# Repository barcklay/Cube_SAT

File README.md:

# HAB-1 — a homemade flight computer for a stratospheric balloon

HAB-1 is an experimental payload for a high-altitude weather balloon. It will climb to
about **30 km**, record what happens on the way up, fall back under a parachute, and then
has to be found on the ground. First flight planned in **Thailand, February–March 2027**.

**Interactive 3D model:** https://claude.ai/artifact/VP8YPhxGNXckYP5Keu93rK
— scrub through the flight, open the box and look at the board inside.
**Code and design files:** https://github.com/barcklay/Cube_SAT (this repository)

<!-- PHOTOS: add docs/photos/bench_top.jpg, docs/photos/modules.jpg, docs/photos/telemetry.jpg
     and a short video link here (Linear HW-157). -->

## About me

I'm Ilzira Badretdinova. I have lived in Bangkok for four years. I design HAB-1 on my own —
the electronics, the firmware, the circuit board and the enclosure — and I would like to
fly it for the first time **together with an experienced team**.

## What already works

Everything below runs today on the bench (NUCLEO-G474RE development board + breadboard
with the real sensor modules) and has been tested:

| Part | What it does | Status |
|---|---|---|
| **STM32G474** firmware | reads all sensors 5 times a second, one telemetry frame every 200 ms | ✅ tested |
| **Barometer** BMP390 | pressure, temperature, altitude (layered standard atmosphere, 0–47 km) | ✅ tested |
| **IMU** ICM-42688 | acceleration and rotation: swing, burst, parachute opening | ✅ tested |
| **GPS** u-blox MAX-M10S | position and altitude; set to *Airborne <4g* so it keeps working above 12 km | ✅ tested on the ground |
| **Outside temperature** DS18B20 | air temperature through the box wall | ✅ tested |
| **Black box** 16 MB SPI flash | every frame logged with a CRC; survives power cuts and resets | ✅ tested |
| **Watchdog + sensor recovery** | a hung program restarts in 2 s; a lost sensor is marked and retried every 5 s | ✅ tested by pulling wires live |
| **Flight state machine** | PRELAUNCH → ASCENT → FLOAT → BURST → DESCENT → LANDED; continues after a reset in flight | ✅ tested in simulation, on the laptop and in a lift |

## Still in development / not tested yet

| Part | Status |
|---|---|
| **LoRa radio** E22-400M22S (433 MHz) and the ground station | ⏳ parts on the way, not brought up yet |
| **Flight PCB** — 4-layer CubeSat 1U board, modules on sockets | designed and routed (ERC/DRC clean), ⏳ independent review, then manufacture |
| **Enclosure** — foam box with a 3D-printed sled | concept ready, not built |
| **Cold test** (dry ice, −60 °C), drop test, tethered flight | ⏳ planned |
| **Backup tracker, recovery buzzer, parachute** | ⏳ to buy / to build |

## Main parameters (preliminary)

| | |
|---|---|
| Payload mass | **≈ 400–600 g** (estimate: ~400 g without a camera, ~600 g with one); weighed after assembly |
| Payload size | **≈ 250 × 175 × 140 mm**, orange foam box (XPS, 30 mm walls) |
| Flight board | 95.9 × 90.2 mm (CubeSat 1U), STM32G474RET6 |
| Power | 4 × Energizer L91 lithium AA (work down to −40 °C), 3.3 V regulator |
| Radio | LoRa 433 MHz (E22-400M22S); output power to be set within Thai (NBTC) limits |
| Tracking and recovery | GPS position over LoRa during the flight; separate backup GPS/SIM tracker with its own battery; buzzer after landing; contact label on the box |
| Balloon / parachute | latex balloon, burst at ~30 km expected; parachute for ~5 m/s at the ground (not chosen yet) |
| Expected flight | ~1 h 40 min up, ~45 min down, landing 30–80 km from the launch point (depends on winds) |

## What the flight should prove

1. The flight computer works end to end in real conditions: cold, low pressure,
   vibration at burst — and recognises every phase of the flight on its own.
2. The black box records the whole flight without gaps.
3. Radio telemetry reaches the ground station, and the payload can be tracked and found.
4. A measured temperature and pressure profile of the tropical atmosphere up to ~30 km
   (the tropopause over Thailand is colder than −75 °C).
5. Photos of the horizon from the stratosphere (if a camera flies).

## What I'm looking for

- **A joint launch**, or a place for HAB-1 in an existing balloon mission.
- **A technical review** of the payload by people who have flown before.
- **Help with permissions**: CAAT (unmanned free balloon), NOTAM, and the radio.
  **I do not have a flight permission yet.**

## Things I found and fixed along the way

- The usual barometric formula is only valid below 11 km: at 30 km it reads **~4.7 km too
  low**. The firmware now uses the layered standard atmosphere.
- A pulled DS18B20 wire read as a perfectly valid **0.0 °C** (all-zero data passes the CRC).
  The firmware now checks bits the sensor always sets.
- The IMU breakout corrupted the flash on a shared SPI bus, so each has its own bus.
- Two of five sensor modules had a different pin order than expected; every socket on the
  PCB was checked against the real module before routing.

## Repository

| Folder | What is inside |
|---|---|
| `hab_bringup/` | STM32 firmware (STM32CubeMX + CMake). Flight logic in `Core/Inc/flight_sm.h` |
| `tools/` | live telemetry viewer, ground station, log download, flashing, the lift test, the state machine test |
| `hardware/flight_pcb/` | flight board: spec, schematic and PCB **generated by Python scripts**, auto-routing with Freerouting, checks |
| `mission/launch_site/` | how the launch site was chosen: airports, military areas, borders, terrain, predicted landing points |
| `portfolio/lab/` | the interactive 3D page |
| `bmp390_altitude/`, `flash_boot_counter/`, `FlashCard/` | first bring-up experiments |

## How it is checked

- **Firmware:** `tools/test_flight_sm.c` flies 10 synthetic balloons through the state
  machine (normal flight, noisy sensor, slow leak, 3 h float, reset in flight,
  stop-and-go ascent…); an accelerated fake flight runs on the real board (`S` command).
- **Board:** KiCad ERC and DRC, a netlist check against the generator's tables, and
  schematic-to-PCB parity — all clean before a change is committed.

```sh
python3 tools/telemetry.py          # live view of the board over USB
python3 tools/logdump.py            # download the black box as CSV
python3 tools/ground_station.py --demo   # ground station on a made-up flight: map, altitude, signal
python3 tools/test_ground_station.py     # packet decoding checked against the firmware's own C code
cc -O2 -o /tmp/t tools/test_flight_sm.c -lm && /tmp/t   # state machine tests
cc -O2 -o /tmp/a tools/test_altitude.c -lm && /tmp/a    # barometer + GPS altitude: flights to 33 km, GPS gaps
cc -O2 -o /tmp/o tools/test_oled.c -lm && /tmp/o        # bench OLED: screens and the piecewise update
```

## Contact

Ilzira Badretdinova, Bangkok · **ilzira.reads@gmail.com** · or open an issue in this repository.

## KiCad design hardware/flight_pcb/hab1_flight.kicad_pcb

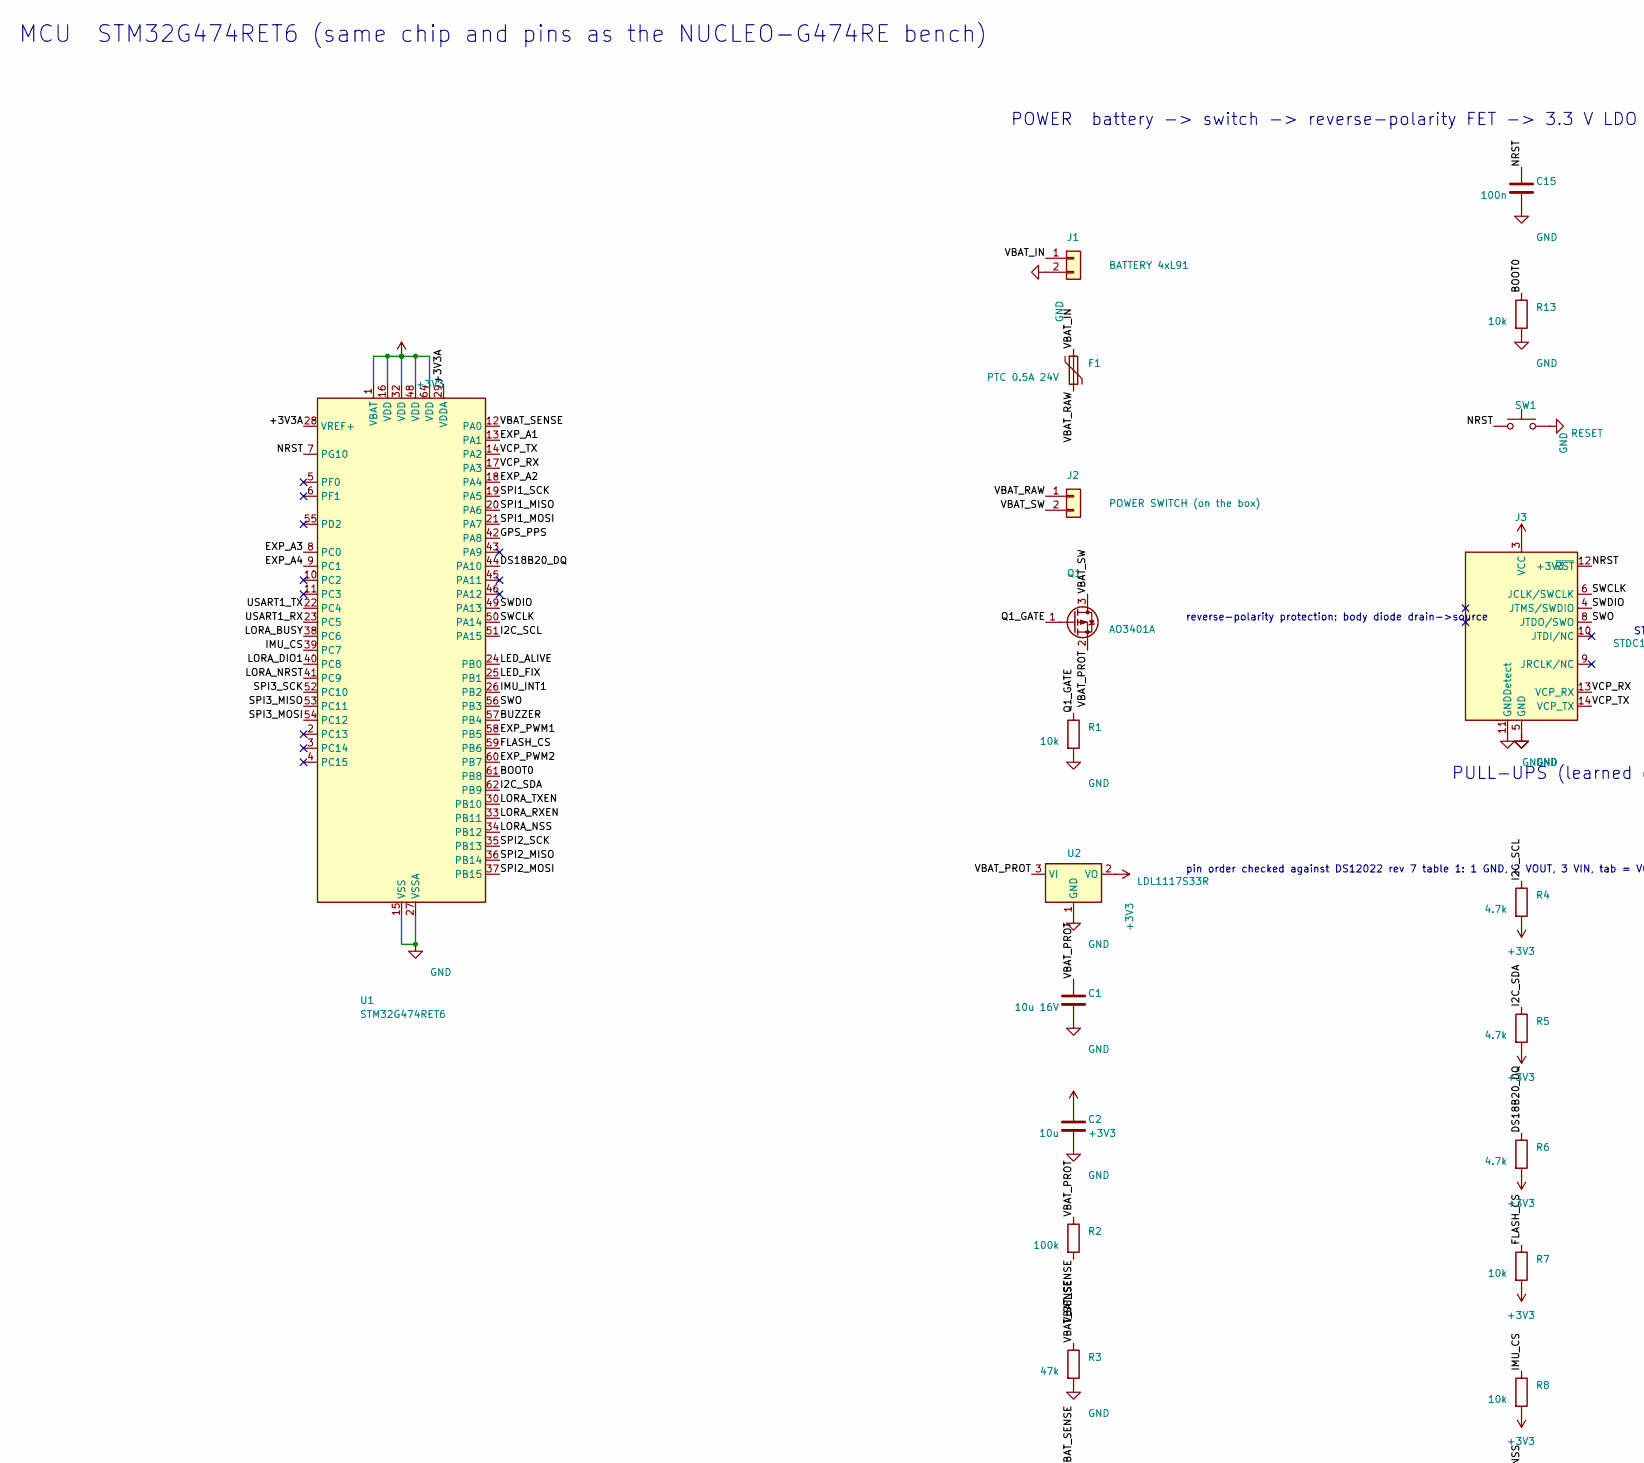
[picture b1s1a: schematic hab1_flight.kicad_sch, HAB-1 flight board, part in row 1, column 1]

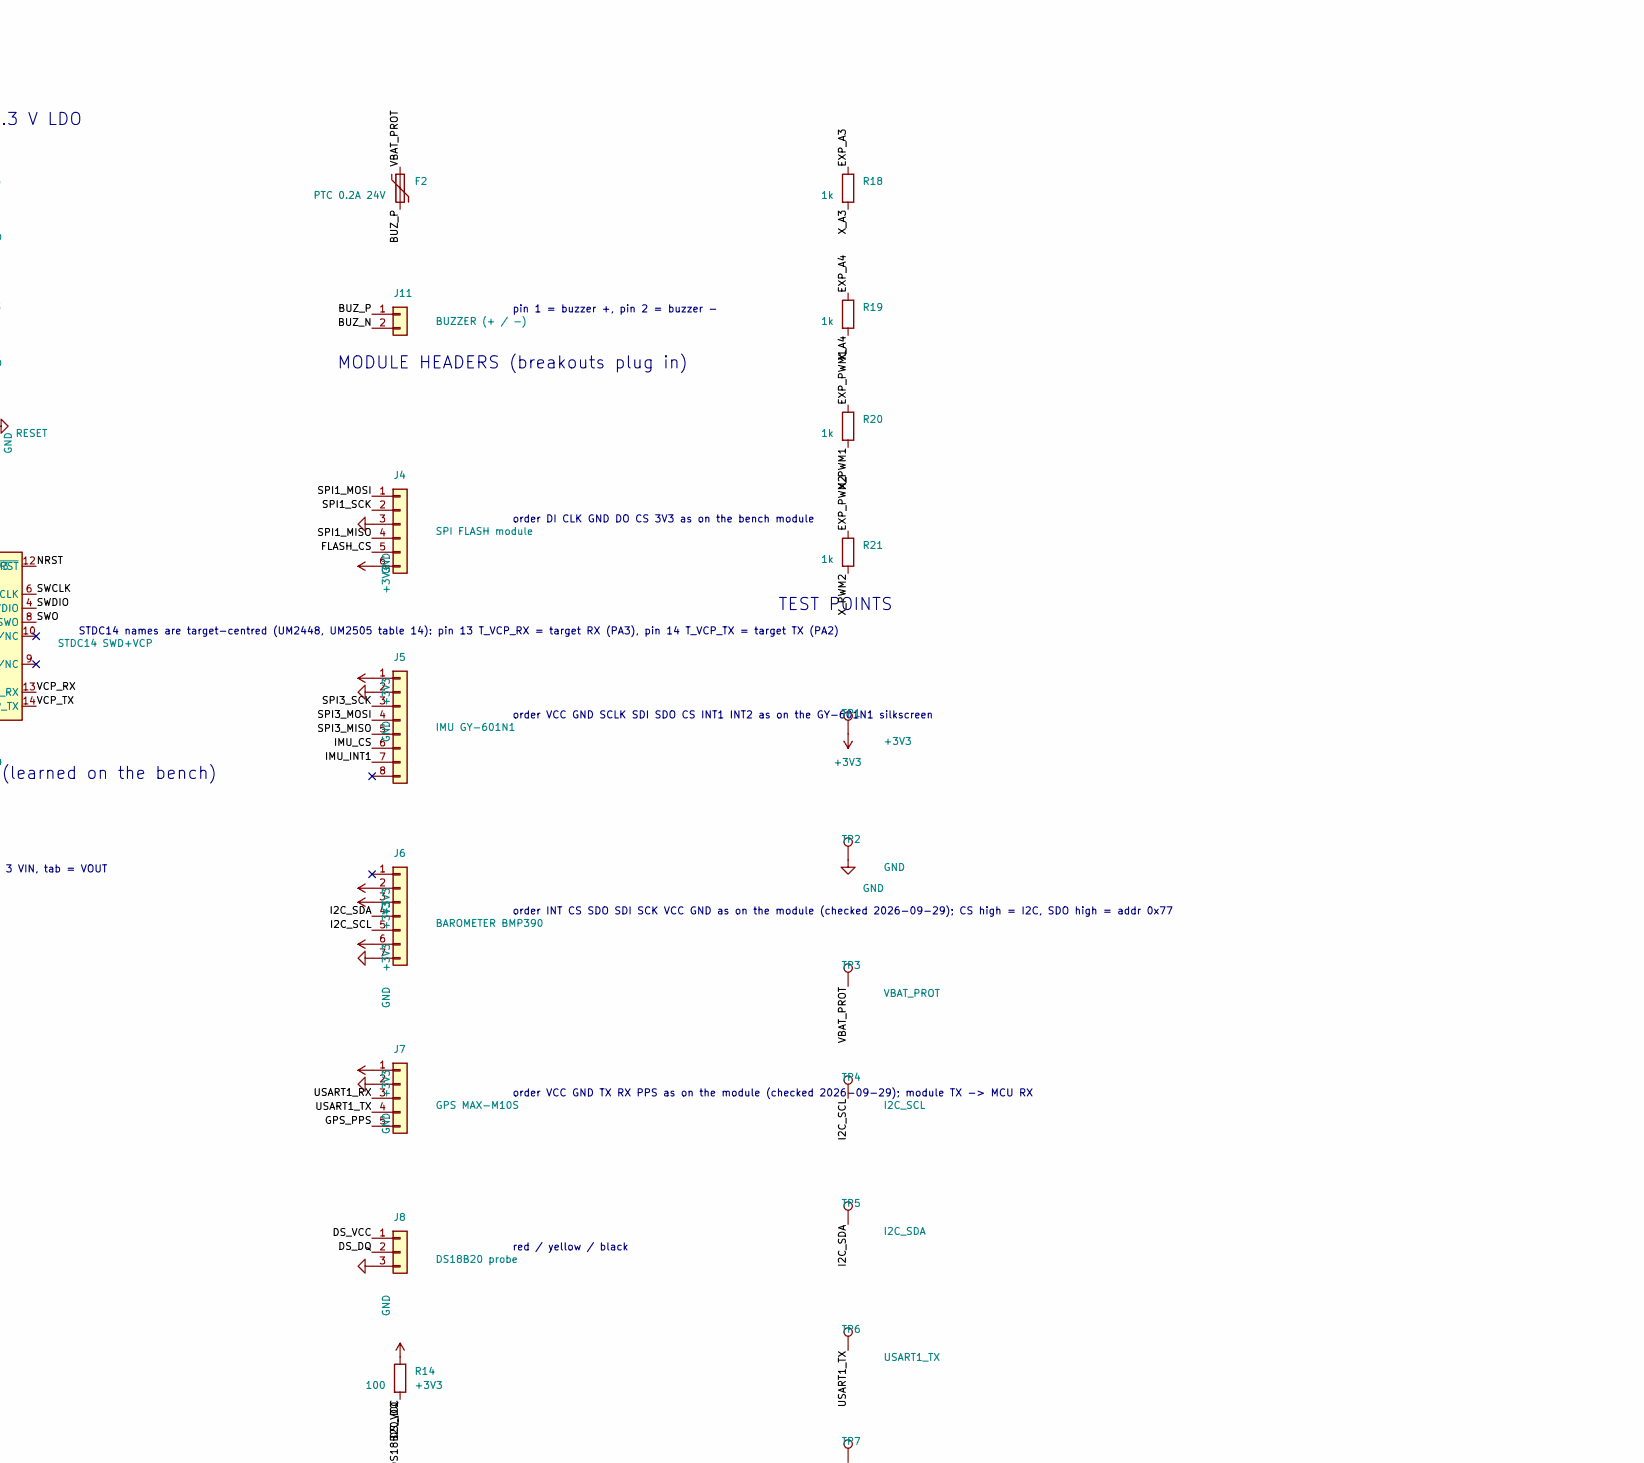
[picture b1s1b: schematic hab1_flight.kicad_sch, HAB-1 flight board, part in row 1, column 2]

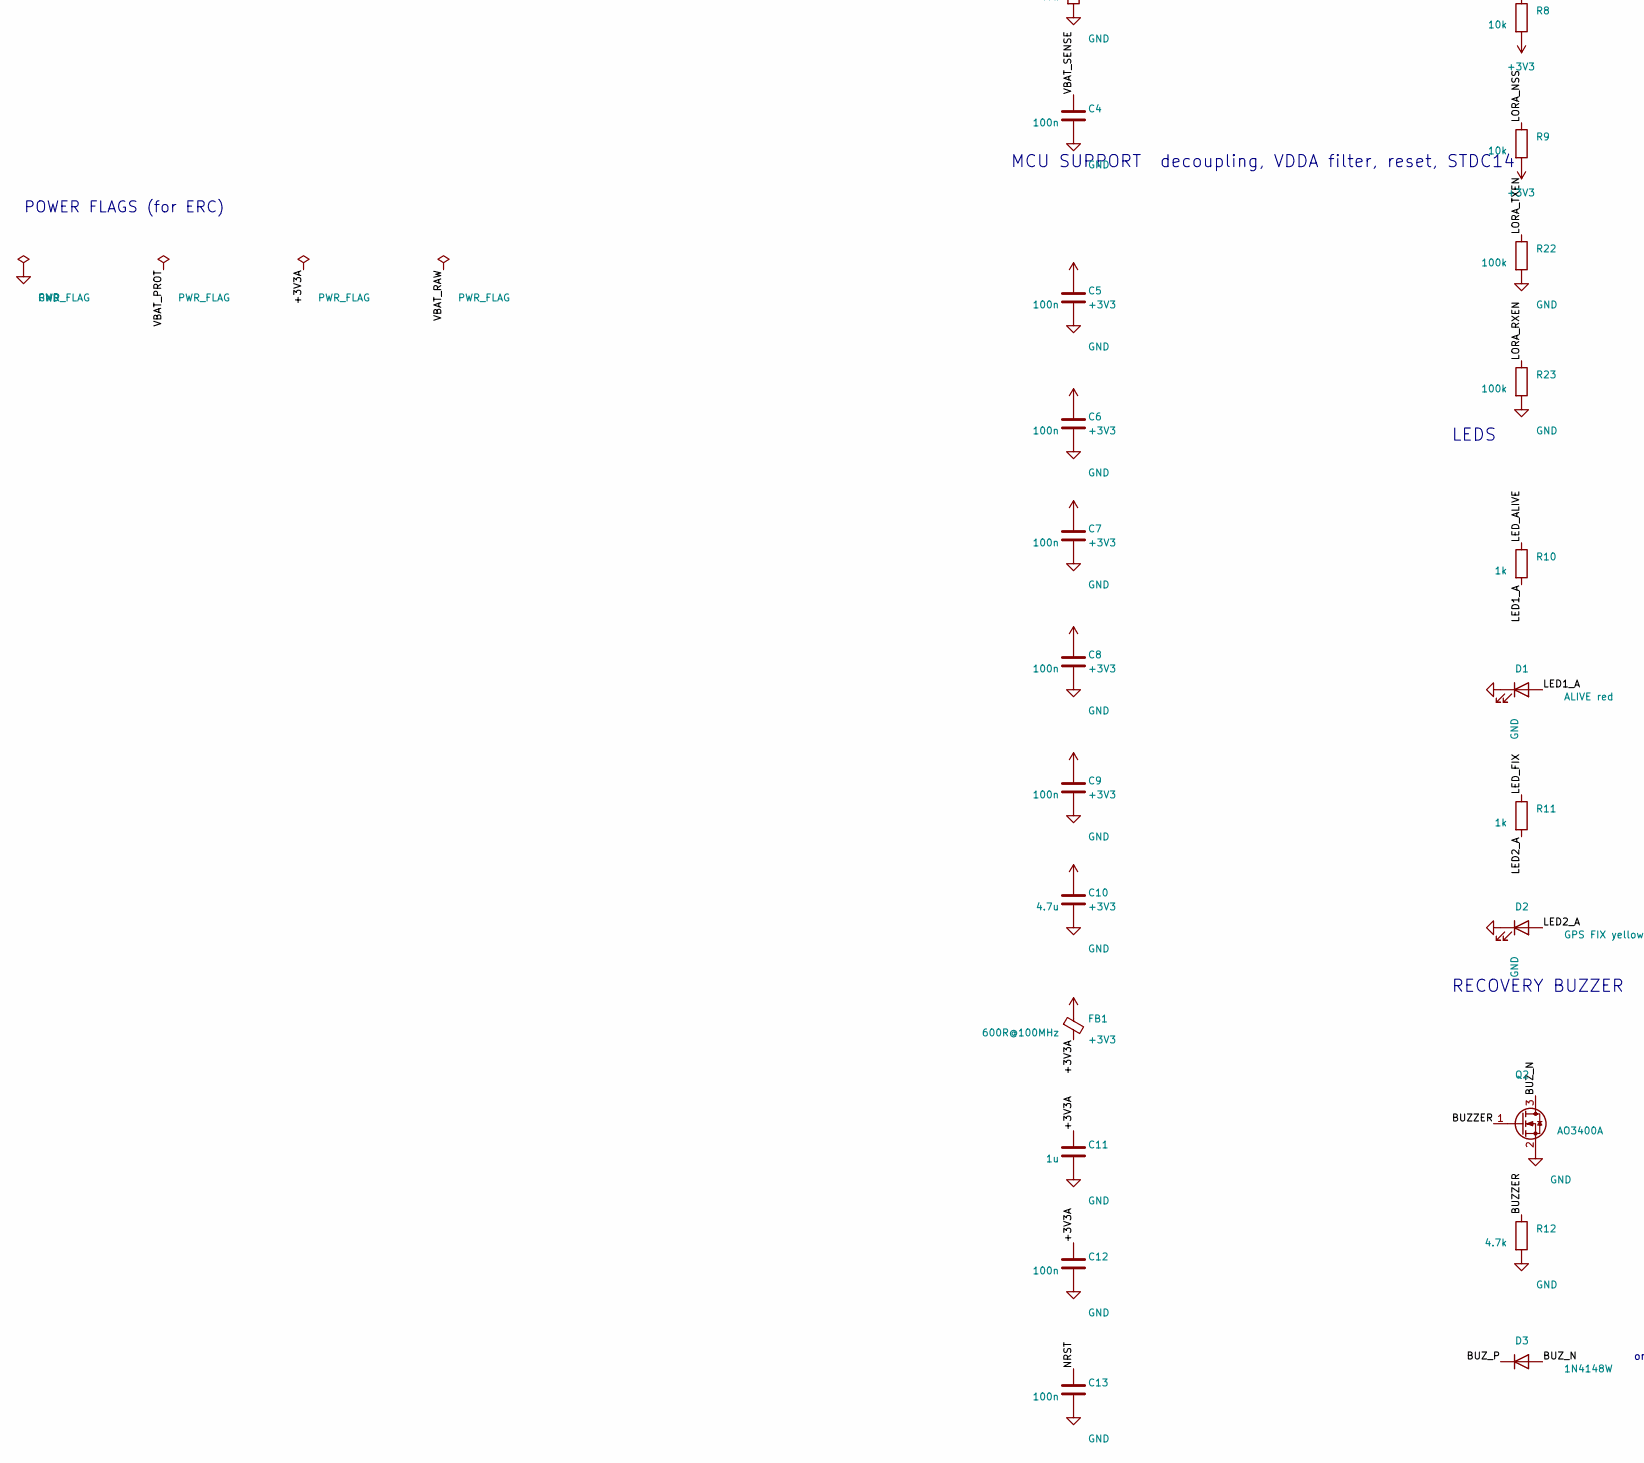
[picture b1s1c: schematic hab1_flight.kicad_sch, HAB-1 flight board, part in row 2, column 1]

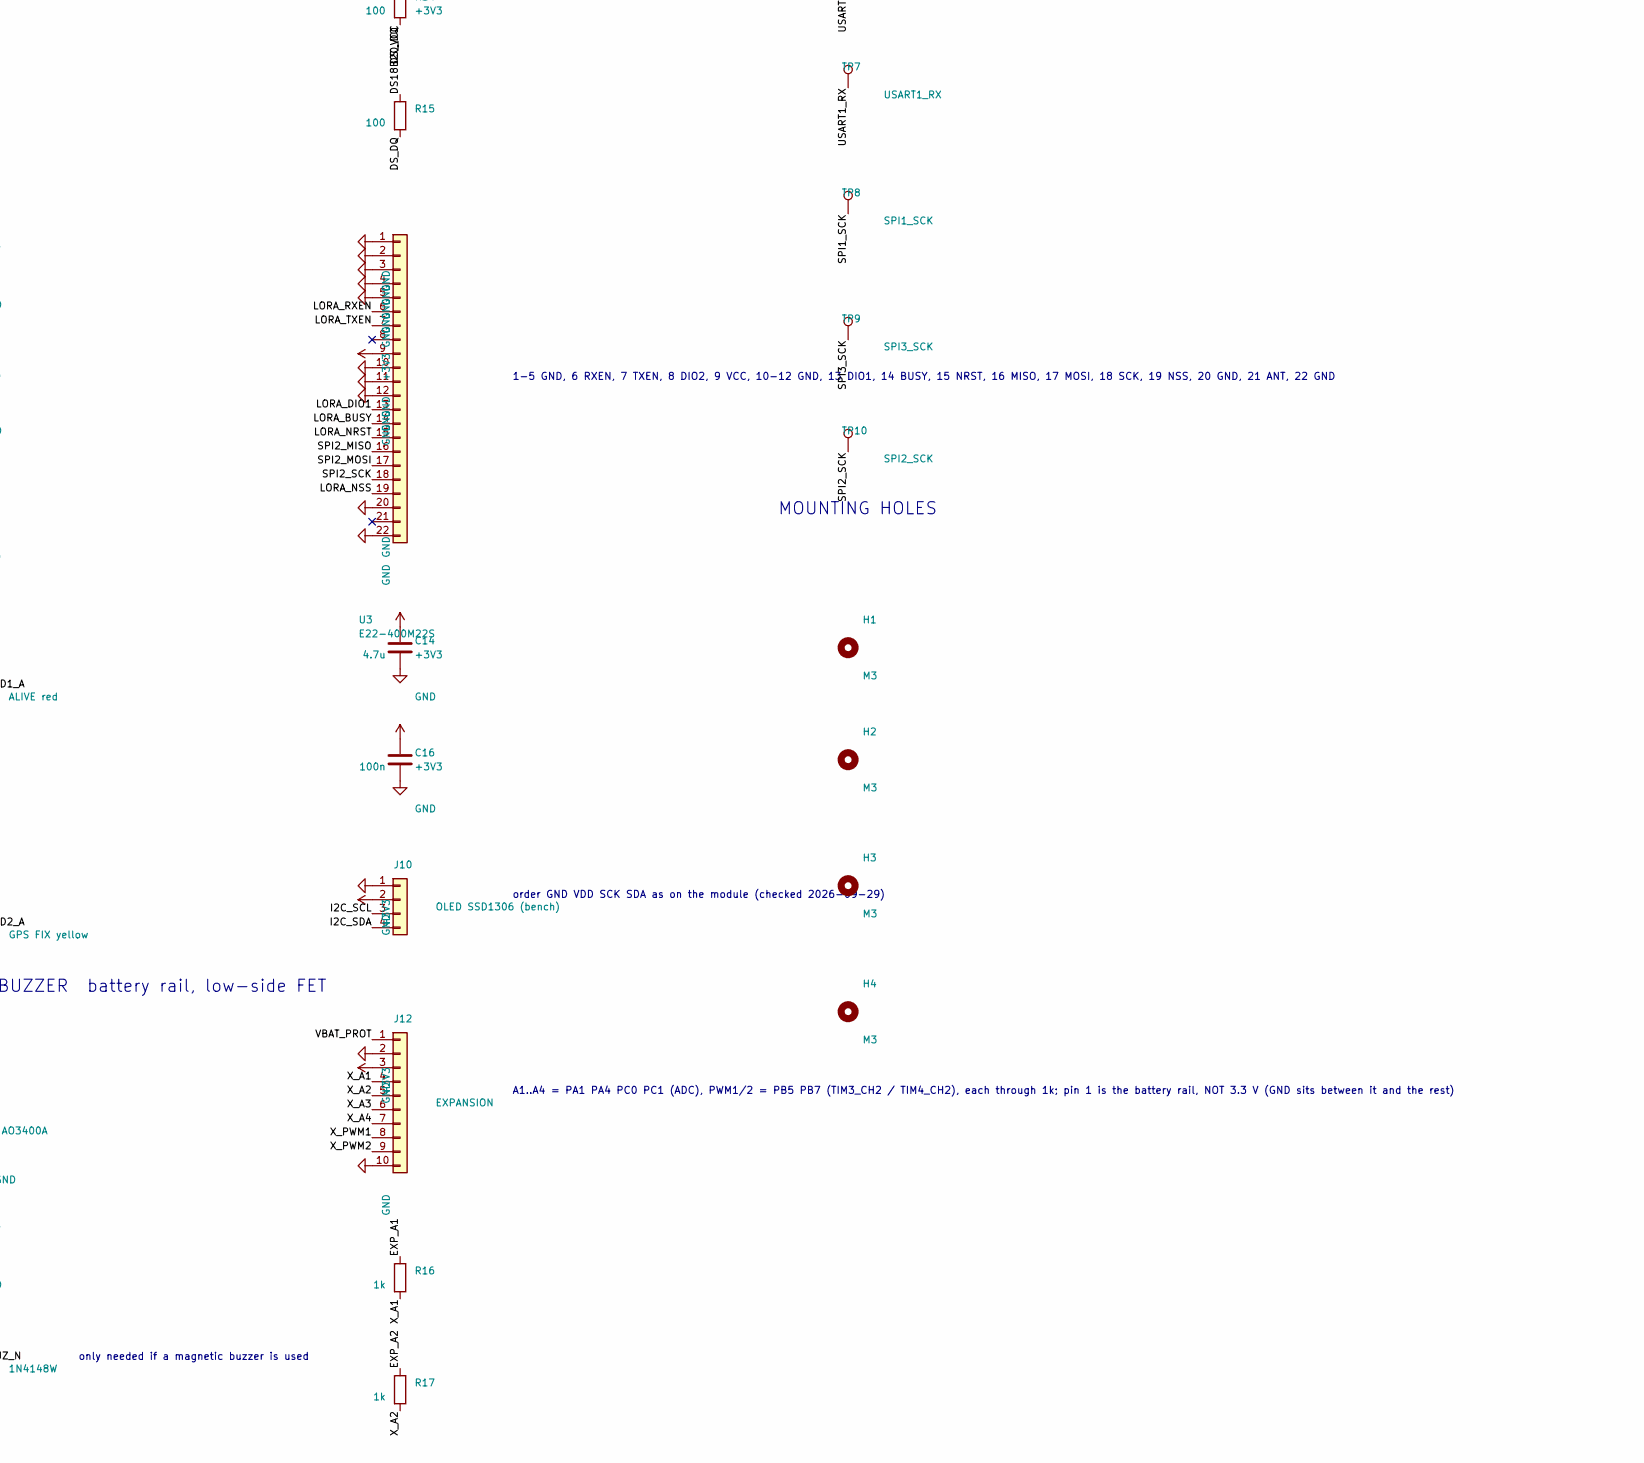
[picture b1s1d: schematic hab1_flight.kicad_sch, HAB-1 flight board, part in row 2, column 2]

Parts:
C1: 10u 16V; C_0805_2012Metric
C2: 10u; C_0805_2012Metric
C4, C5, C6, C7, C8, C9, C12, C13, C15, C16: 100n; C_0603_1608Metric
C10, C14: 4.7u; C_0805_2012Metric
C11: 1u; C_0603_1608Metric
D1: ALIVE red; LED_0603_1608Metric
D2: GPS FIX yellow; LED_0603_1608Metric
D3: 1N4148W; D_SOD-123
F1: PTC 0.5A 24V; Fuse_1206_3216Metric
F2: PTC 0.2A 24V; Fuse_1206_3216Metric
FB1: 600R@100MHz; L_0603_1608Metric
H1, H2, H3, H4: M3; MountingHole_3.2mm_M3
J1: BATTERY 4xL91; JST_XH_B2B-XH-A_1x02_P2.50mm_Vertical
J2: POWER SWITCH (on the box); JST_XH_B2B-XH-A_1x02_P2.50mm_Vertical
J3: STDC14 SWD+VCP; PinHeader_2x07_P1.27mm_Vertical_SMD
J4: SPI FLASH module; PinSocket_1x06_P2.54mm_Vertical
J5: IMU GY-601N1; PinSocket_1x08_P2.54mm_Vertical
J6: BAROMETER BMP390; PinSocket_1x07_P2.54mm_Vertical
J7: GPS MAX-M10S; PinSocket_1x05_P2.54mm_Vertical
J8: DS18B20 probe; JST_XH_B3B-XH-A_1x03_P2.50mm_Vertical
J10: OLED SSD1306 (bench); PinSocket_1x04_P2.54mm_Vertical
J11: BUZZER (+ / -); JST_XH_B2B-XH-A_1x02_P2.50mm_Vertical
J12: EXPANSION; PinSocket_1x10_P2.54mm_Vertical
Q1: AO3401A; SOT-23
Q2: AO3400A; SOT-23
R1, R7, R8, R9, R13: 10k; R_0603_1608Metric
R2, R22, R23: 100k; R_0603_1608Metric
R3: 47k; R_0603_1608Metric
R4, R5, R6, R12: 4.7k; R_0603_1608Metric
R10, R11, R16, R17, R18, R19, R20, R21: 1k; R_0603_1608Metric
R14, R15: 100; R_0603_1608Metric
SW1: RESET; SW_SPST_TL3342
TP1: +3V3; TestPoint_Pad_D1.5mm
TP2: GND; TestPoint_Pad_D1.5mm
TP3: VBAT_PROT; TestPoint_Pad_D1.5mm
TP4: I2C_SCL; TestPoint_Pad_D1.5mm
TP5: I2C_SDA; TestPoint_Pad_D1.5mm
TP6: USART1_TX; TestPoint_Pad_D1.5mm
TP7: USART1_RX; TestPoint_Pad_D1.5mm
TP8: SPI1_SCK; TestPoint_Pad_D1.5mm
TP9: SPI3_SCK; TestPoint_Pad_D1.5mm
TP10: SPI2_SCK; TestPoint_Pad_D1.5mm
U1: STM32G474RET6; LQFP-64_10x10mm_P0.5mm
U2: LDL1117S33R; SOT-223-3_TabPin2
U3: E22-400M22S

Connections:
+3V3: C2.1, C5.1, C6.1, C7.1, C8.1, C9.1, C10.1, C14.1, C16.1, FB1.1, J3.3 (VCC), J4.6, J5.1, J6.2, J6.3, J6.6, J7.1, J10.2, J12.3, R4.2, R5.2, R6.2, R7.2, R8.2, R9.2, R14.1, TP1.1, U1.1 (VBAT), U1.16 (VDD), U1.32 (VDD), U1.48 (VDD), U1.64 (VDD), U2.2 (VO), U3.9
/+3V3A: C11.1, C12.1, FB1.2, U1.28 (VREF+), U1.29 (VDDA)
/BOOT0: R13.1, U1.61 (PB8)
/BUZZER: Q2.1 (G), R12.1, U1.57 (PB4)
/BUZ_N: D3.2 (A), J11.2, Q2.3 (D)
/BUZ_P: D3.1 (K), F2.2, J11.1
/DS18B20_DQ: R6.1, R15.1, U1.44 (PA10)
/DS_DQ: J8.2, R15.2
/DS_VCC: J8.1, R14.2
/EXP_A1: R16.1, U1.13 (PA1)
/EXP_A2: R17.1, U1.18 (PA4)
/EXP_A3: R18.1, U1.8 (PC0)
/EXP_A4: R19.1, U1.9 (PC1)
/EXP_PWM1: R20.1, U1.58 (PB5)
/EXP_PWM2: R21.1, U1.60 (PB7)
/FLASH_CS: J4.5, R7.1, U1.59 (PB6)
/GPS_PPS: J7.5, U1.42 (PA8)
/I2C_SCL: J6.5, J10.3, R4.1, TP4.1, U1.51 (PA15)
/I2C_SDA: J6.4, J10.4, R5.1, TP5.1, U1.62 (PB9)
/IMU_CS: J5.6, R8.1, U1.39 (PC7)
/IMU_INT1: J5.7, U1.26 (PB2)
/LED1_A: D1.2 (A), R10.2
/LED2_A: D2.2 (A), R11.2
/LED_ALIVE: R10.1, U1.24 (PB0)
/LED_FIX: R11.1, U1.25 (PB1)
/LORA_BUSY: U1.38 (PC6), U3.14
/LORA_DIO1: U1.40 (PC8), U3.13
/LORA_NRST: U1.41 (PC9), U3.15
/LORA_NSS: R9.1, U1.34 (PB12), U3.19
/LORA_RXEN: R23.1, U1.33 (PB11), U3.6
/LORA_TXEN: R22.1, U1.30 (PB10), U3.7
/NRST: C13.1, C15.1, J3.12 (~RST), SW1.1, U1.7 (PG10)
/Q1_GATE: Q1.1 (G), R1.1
/SPI1_MISO: J4.4, U1.20 (PA6)
/SPI1_MOSI: J4.1, U1.21 (PA7)
/SPI1_SCK: J4.2, TP8.1, U1.19 (PA5)
/SPI2_MISO: U1.36 (PB14), U3.16
/SPI2_MOSI: U1.37 (PB15), U3.17
/SPI2_SCK: TP10.1, U1.35 (PB13), U3.18
/SPI3_MISO: J5.5, U1.53 (PC11)
/SPI3_MOSI: J5.4, U1.54 (PC12)
/SPI3_SCK: J5.3, TP9.1, U1.52 (PC10)
/SWCLK: J3.6 (JCLK/SWCLK), U1.50 (PA14)
/SWDIO: J3.4 (JTMS/SWDIO), U1.49 (PA13)
/SWO: J3.8 (JTDO/SWO), U1.56 (PB3)
/USART1_RX: J7.3, TP7.1, U1.23 (PC5)
/USART1_TX: J7.4, TP6.1, U1.22 (PC4)
/VBAT_IN: F1.1, J1.1
/VBAT_PROT: C1.1, F2.1, J12.1, Q1.2 (S), R2.1, TP3.1, U2.3 (VI)
/VBAT_RAW: F1.2, J2.1
/VBAT_SENSE: C4.1, R2.2, R3.1, U1.12 (PA0)
/VBAT_SW: J2.2, Q1.3 (D)
/VCP_RX: J3.13 (VCP_RX), U1.17 (PA3)
/VCP_TX: J3.14 (VCP_TX), U1.14 (PA2)
/X_A1: J12.4, R16.2
/X_A2: J12.5, R17.2
/X_A3: J12.6, R18.2
/X_A4: J12.7, R19.2
/X_PWM1: J12.8, R20.2
/X_PWM2: J12.9, R21.2
GND: C1.2, C2.2, C4.2, C5.2, C6.2, C7.2, C8.2, C9.2, C10.2, C11.2, C12.2, C13.2, C14.2, C15.2, C16.2, D1.1 (K), D2.1 (K), J1.2, J3.5 (GND), J3.7 (GND), J3.11 (GNDDetect), J4.3, J5.2, J6.7, J7.2, J8.3, J10.1, J12.2, J12.10, Q2.2 (S), R1.2, R3.2, R12.2, R13.2, R22.2, R23.2, SW1.2, TP2.1, U1.15 (VSS), U1.27 (VSSA), U1.31 (VSS), U1.47 (VSS), U1.63 (VSS), U2.1 (GND), U3.1, U3.2, U3.3, U3.4, U3.5, U3.10, U3.11, U3.12, U3.20, U3.22

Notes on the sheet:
MCU STM32G474RET6 (same chip and pins as the NUCLEO-G474RE bench)
POWER battery -> switch -> reverse-polarity FET -> 3.3 V LDO
reverse-polarity protection: body diode drain->source
pin order checked against DS12022 rev 7 table 1: 1 GND, 2 VOUT, 3 VIN, tab = VOUT
MCU SUPPORT decoupling, VDDA filter, reset, STDC14
STDC14 names are target-centred (UM2448, UM2505 table 14): pin 13 T_VCP_RX = target RX (PA3), pin 14 T_VCP_TX = target TX (PA2)
PULL-UPS (learned on the bench)
LEDS
RECOVERY BUZZER battery rail, low-side FET
only needed if a magnetic buzzer is used
pin 1 = buzzer +, pin 2 = buzzer -
MODULE HEADERS (breakouts plug in)
order DI CLK GND DO CS 3V3 as on the bench module
order VCC GND SCLK SDI SDO CS INT1 INT2 as on the GY-601N1 silkscreen
order INT CS SDO SDI SCK VCC GND as on the module (checked 2026-09-29); CS high = I2C, SDO high = addr 0x77
order VCC GND TX RX PPS as on the module (checked 2026-09-29); module TX -> MCU RX
red / yellow / black
1-5 GND, 6 RXEN, 7 TXEN, 8 DIO2, 9 VCC, 10-12 GND, 13 DIO1, 14 BUSY, 15 NRST, 16 MISO, 17 MOSI, 18 SCK, 19 NSS, 20 GND, 21 ANT, 22 GND
order GND VDD SCK SDA as on the module (checked 2026-09-29)
A1..A4 = PA1 PA4 PC0 PC1 (ADC), PWM1/2 = PB5 PB7 (TIM3_CH2 / TIM4_CH2), each through 1k; pin 1 is the battery rail, NOT 3.3 V (GND sits between it and the rest)
TEST POINTS
MOUNTING HOLES
POWER FLAGS (for ERC)

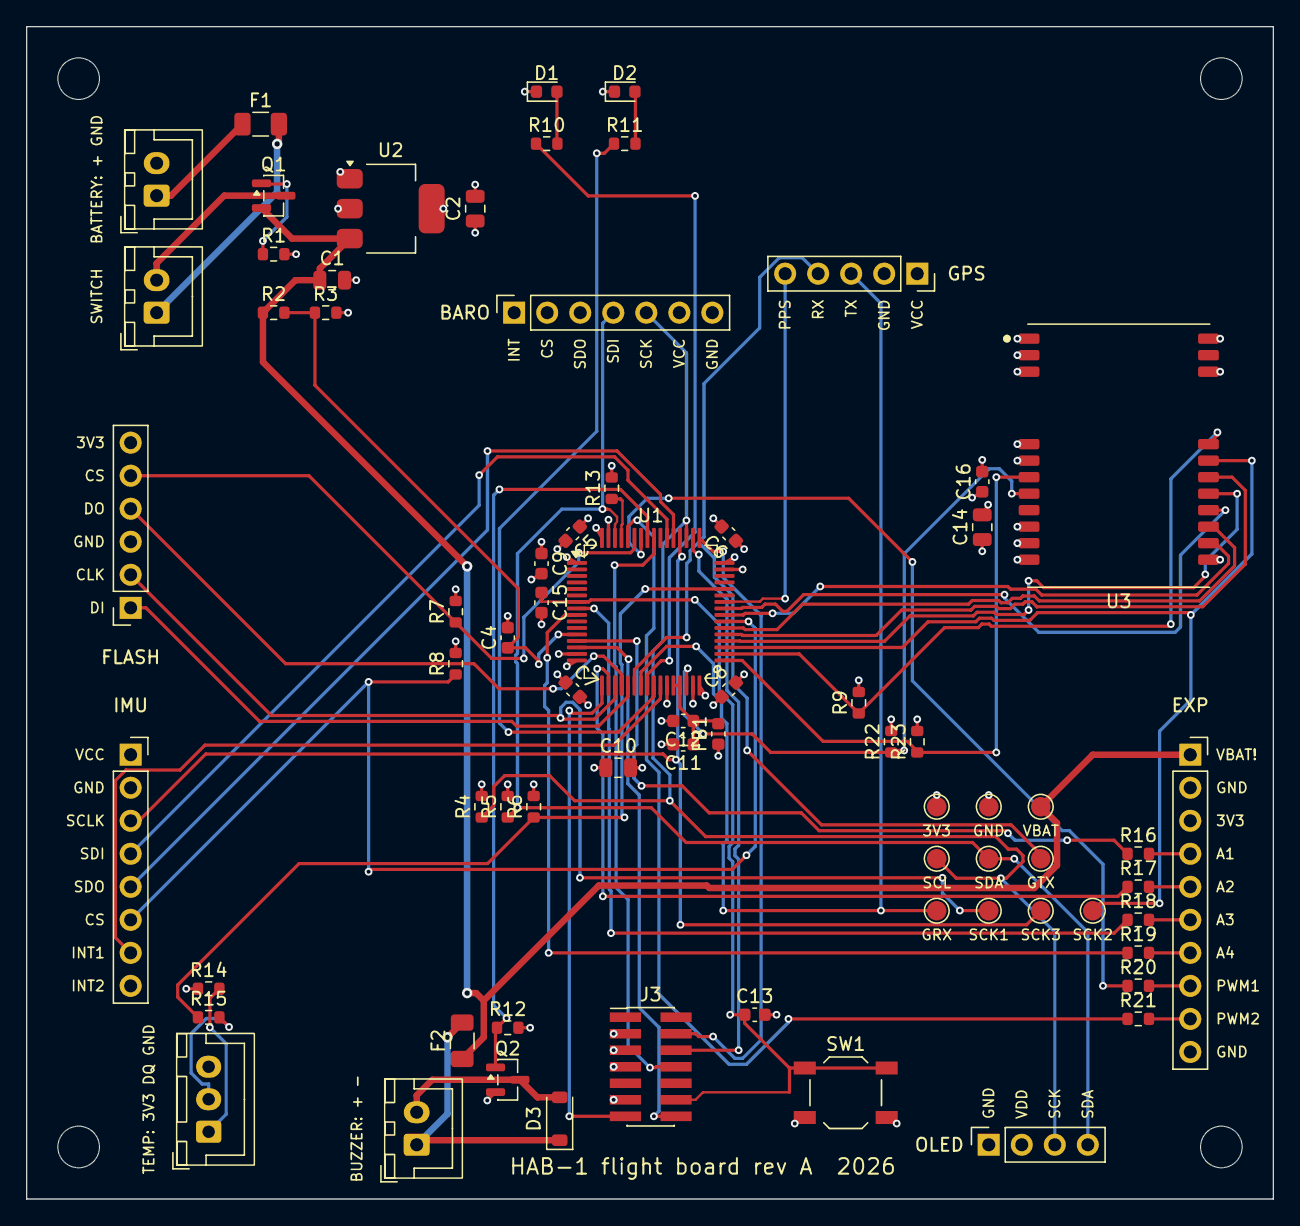
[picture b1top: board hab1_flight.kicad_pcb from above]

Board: 4 copper layers, 95.9 x 90.2 mm, 75 parts (0 on the bottom side), 61 nets.

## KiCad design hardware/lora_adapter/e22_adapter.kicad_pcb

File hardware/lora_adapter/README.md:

# E22-400M22S breakout board

The Ebyte E22-400M22S LoRa module has castellated pads at 1.27 mm pitch: it fits neither a
breadboard nor jumper wires, and no ready adapter with 2.54 mm pins is sold for it. This small
board (31.6 x 25.2 mm, 2 layers) brings every pin out to two rows of ordinary pins 0.8 inch
(20.32 mm) apart, so it plugs into a breadboard. It is for the bench and the ground station;
the flight board carries the module itself.

| Left row, top to bottom | Right row, top to bottom |
|---|---|
| GND | GND |
| DIO1 | 3V3 (the module allows 3.7 V at most) |
| BUSY | DIO2 |
| NRST | TXEN |
| MISO | RXEN |
| MOSI | GND |
| SCK | GND |
| NSS | GND |

On the board: the module, 4.7 uF + 100 nF at its supply pin, ground pours on both sides, no
tracks under the module on the top side. The antenna goes on the module's own IPX connector.

## Files

`python3 gen_adapter.py` (KiCad's Python) builds everything: `e22_adapter.kicad_pcb` and, in
`fab/`, the gerber zip, BOM and CPL for JLCPCB. JLCPCB solders the module (LCSC C411291) and the
two capacitors; the two 1x8 pin rows are soldered by hand, pins pointing down.

Checked: DRC without errors (one cosmetic silkscreen note), 0 unconnected. Not checked: a real
order; the rotation of the module in the CPL (look at the placement picture in the order form:
the pin-1 dot is at the bottom right, the antenna connector at the bottom left).

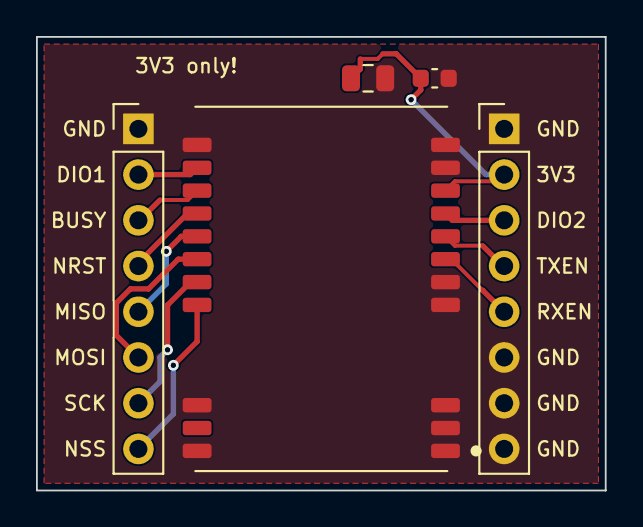
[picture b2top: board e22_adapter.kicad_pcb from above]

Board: 2 copper layers, 31.6 x 25.2 mm, 5 parts (0 on the bottom side), 12 nets.

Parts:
C1: 4.7u; C_0805_2012Metric
C2: 100n; C_0603_1608Metric
J1: LEFT; PinHeader_1x08_P2.54mm_Vertical
J2: RIGHT; PinHeader_1x08_P2.54mm_Vertical
U1: E22-400M22S

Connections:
3V3: C1.1, C2.1, J2.2, U1.9
BUSY: J1.3, U1.14
DIO1: J1.2, U1.13
DIO2: J2.3, U1.8
GND: C1.2, C2.2, J1.1, J2.1, J2.6, J2.7, J2.8, U1.1, U1.2, U1.3, U1.4, U1.5, U1.10, U1.11, U1.12, U1.20, U1.22
MISO: J1.5, U1.16
MOSI: J1.6, U1.17
NRST: J1.4, U1.15
NSS: J1.8, U1.19
RXEN: J2.5, U1.6
SCK: J1.7, U1.18
TXEN: J2.4, U1.7

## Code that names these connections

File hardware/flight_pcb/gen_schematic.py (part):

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# 1. Microcontroller pin -> net (from hab_bringup.ioc, plus the NEW pins of SPEC.md)
# --------------------------------------------------------------------------------------
MCU_NETS = {
    "PA13": "SWDIO", "PA14": "SWCLK", "PB3": "SWO",
    "PG10": "NRST",                                   # pin 7 = PG10-NRST (named "PG10" in KiCad)
    "PA2": "VCP_TX", "PA3": "VCP_RX",                 # LPUART1 console
    # I2C1_SCL is on PA15, not on PB8 as on the Nucleo bench: PB8 is BOOT0, and a pull-up there
    # makes a factory-fresh chip start its ROM bootloader. PB8 is pulled down instead (R13).
    "PA15": "I2C_SCL", "PB9": "I2C_SDA",              # barometer, OLED
    "PB8": "BOOT0",
    "PA5": "SPI1_SCK", "PA6": "SPI1_MISO", "PA7": "SPI1_MOSI", "PB6": "FLASH_CS",
    "PC10": "SPI3_SCK", "PC11": "SPI3_MISO", "PC12": "SPI3_MOSI", "PC7": "IMU_CS",
    "PB2": "IMU_INT1",
    "PC4": "USART1_TX", "PC5": "USART1_RX",           # GPS
    "PA8": "GPS_PPS",                                  # GPS 1 pulse per second (TIM1_CH1)
    "PB4": "BUZZER",                                   # recovery buzzer (TIM3_CH1 if a passive one)
    "PA10": "DS18B20_DQ",
    "PB13": "SPI2_SCK", "PB14": "SPI2_MISO", "PB15": "SPI2_MOSI", "PB12": "LORA_NSS",
    "PC6": "LORA_BUSY", "PC8": "LORA_DIO1", "PC9": "LORA_NRST",
    "PB10": "LORA_TXEN", "PB11": "LORA_RXEN",
    "PA0": "VBAT_SENSE", "PB0": "LED_ALIVE", "PB1": "LED_FIX",
    # spare pins on the expansion header J12: 4 analog-capable, 2 timer (PWM) outputs
    "PA1": "EXP_A1", "PA4": "EXP_A2", "PC0": "EXP_A3", "PC1": "EXP_A4",
    "PB5": "EXP_PWM1", "PB7": "EXP_PWM2",
}
MCU_POWER = {"VDD": "+3V3", "VBAT": "+3V3", "VSS": "GND", "VSSA": "GND",
             "VDDA": "+3V3A", "VREF+": "+3V3A"}
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      "8": "SWO", "9": None, "10": None, "11": "GND", "12": "NRST",
      "13": "VCP_RX", "14": "VCP_TX"}, "mcu",
     "STDC14 names are target-centred (UM2448, UM2505 table 14): pin 13 T_VCP_RX = target RX "
     "(PA3), pin 14 T_VCP_TX = target TX (PA2)")

# Pull-ups learned on the bench
r("R4", "4.7k", "I2C_SCL", "+3V3", "pullups")
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part("D2", "Device:LED", "GPS FIX yellow", "LED_SMD:LED_0603_1608Metric",
     {"1": "GND", "2": "LED2_A"}, "leds")

# Recovery buzzer: an active piezo buzzer (3-24 V) on a 2-pin cable to the box wall,
# switched on the low side from the battery rail so it is loud; beeps only after LANDED.
part("Q2", "Transistor_FET:AO3400A", "AO3400A", "Package_TO_SOT_SMD:SOT-23",
     {"1": "BUZZER", "2": "GND", "3": "BUZ_N"}, "buzzer")
# 4.7k, not 100k: after reset PB4 is NJTRST with a ~40k internal pull-up, which would lift a
# 100k-pulled gate above the FET threshold and sound the buzzer during reset / in the bootloader
r("R12", "4.7k", "BUZZER", "GND", "buzzer")
part("D3", "Device:D", "1N4148W", "Diode_SMD:D_SOD-123",
     {"1": "BUZ_P", "2": "BUZ_N"}, "buzzer", "only needed if a magnetic buzzer is used")
# the buzzer cable leaves the box: its own small fuse, so a pinched cable does not end the flight
part("F2", "Device:Polyfuse", "PTC 0.2A 24V", "Fuse:Fuse_1206_3216Metric",
     {"1": "VBAT_PROT", "2": "BUZ_P"}, "buzzer")
part("J11", "Connector_Generic:Conn_01x02", "BUZZER (+ / -)", XH.format(n=2),
     {"1": "BUZ_P", "2": "BUZ_N"}, "buzzer", "pin 1 = buzzer +, pin 2 = buzzer -")

# Module headers (female sockets on the board)
part("J4", "Connector_Generic:Conn_01x06", "SPI FLASH module", SOCK.format(n=6),
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     "order VCC GND TX RX PPS as on the module (checked 2026-09-29); module TX -> MCU RX")
part("J8", "Connector_Generic:Conn_01x03", "DS18B20 probe", XH.format(n=3),
     {"1": "DS_VCC", "2": "DS_DQ", "3": "GND"}, "modules", "red / yellow / black")
# the probe cable leaves the box: a short on it must not pull the 3V3 rail down or hit PA10 directly
r("R14", "100", "+3V3", "DS_VCC", "modules")
r("R15", "100", "DS18B20_DQ", "DS_DQ", "modules")
# LoRa module soldered straight onto the board by JLCPCB (LCSC C411291): no adapter, no socket.
# Pin numbers and names from the Ebyte E22-400M22S manual v1.2 section 3, the same as the
# labels on the back of the real module. DIO2 is not used (TXEN/RXEN are driven by the MCU);
# ANT (pin 21) stays open: the antenna goes on the module's own IPX connector.
part("U3", "Connector_Generic:Conn_01x22", "E22-400M22S", "hab1:E22-400M22S",
     {"1": "GND", "2": "GND", "3": "GND", "4": "GND", "5": "GND", "6": "LORA_RXEN",
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part("J12", "Connector_Generic:Conn_01x10", "EXPANSION", SOCK.format(n=10),
     {"1": "VBAT_PROT", "2": "GND", "3": "+3V3", "4": "X_A1", "5": "X_A2", "6": "X_A3",
      "7": "X_A4", "8": "X_PWM1", "9": "X_PWM2", "10": "GND"}, "modules",
     "A1..A4 = PA1 PA4 PC0 PC1 (ADC), PWM1/2 = PB5 PB7 (TIM3_CH2 / TIM4_CH2), each through 1k; "
     "pin 1 is the battery rail, NOT 3.3 V (GND sits between it and the rest)")
for i, sig in enumerate(["A1", "A2", "A3", "A4", "PWM1", "PWM2"]):
    r(f"R{16 + i}", "1k", f"EXP_{sig}", f"X_{sig}", "modules")
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
done = set(bussed)
for num, (x, y, ang, name, typ) in sorted(mcu.items()):
    # a pin name can carry several functions: "PB8-BOOT0", "PG10-NRST", "PC14-OSC32_IN"
    net = next((MCU_NETS[x] for x in [name] + name.split("-") if x in MCU_NETS), None) \
        or MCU_POWER.get(name)
    if (x, y) in done:
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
